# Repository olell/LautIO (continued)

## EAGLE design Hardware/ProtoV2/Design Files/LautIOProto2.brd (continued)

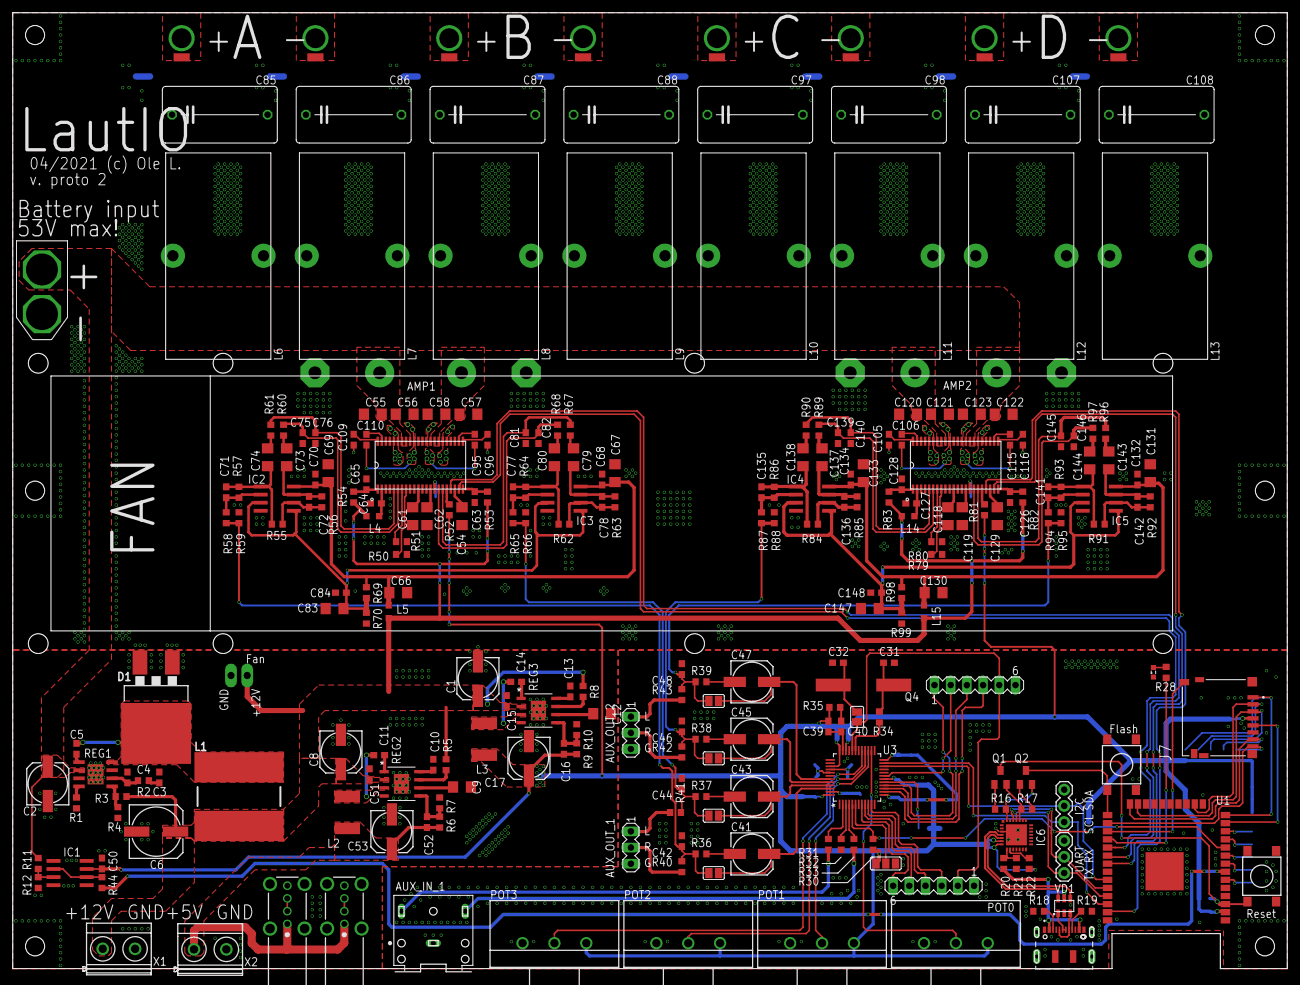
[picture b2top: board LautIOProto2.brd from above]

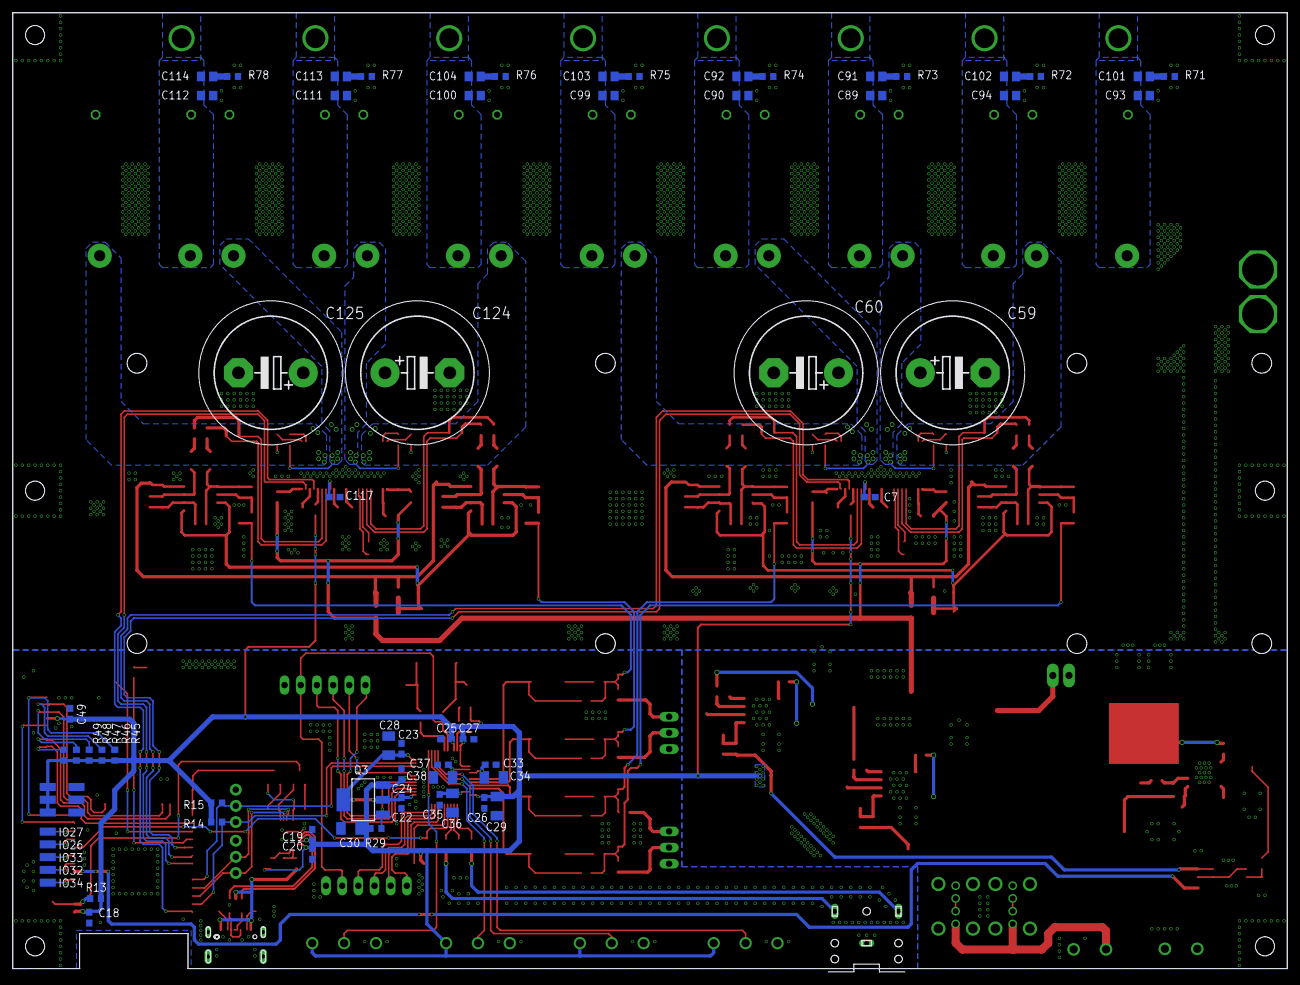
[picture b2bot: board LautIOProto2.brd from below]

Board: 2 copper layers, 200.0 x 150.5 mm, 322 parts (70 on the bottom side), 199 nets.

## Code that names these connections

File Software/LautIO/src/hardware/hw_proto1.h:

/*
 *
 * This file is part of LautIO
 * 
 * Copyright 2021 - olel
 * LautIO is licensed under MIT License
 * See LICENSE file for more information
 * 
 */

#pragma once

// Amp AB Controls
#define AMP_AB_MUTE_PIN    17 // IO17
#define AMP_AB_STANDBY_PIN 16 // IO16

// Amp CD Controls
#define AMP_CD_MUTE_PIN    33 // IO33
#define AMP_CD_STANDBY_PIN 32 // IO32

// DSP Controls
#define DSP_RESET_PIN      14 // IO14

// I2S Output
#define DSP_IN_DATA_PIN    26 // IO26
#define DSP_IN_BCLK_PIN    27 // IO27
#define DSP_IN_LRCLK_PIN   13 // IO13

//#define HARDWARE_HAS_SDCARD // Uncomment on hardware versions which have sd card slots

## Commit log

2021-03-09 Added some files
2021-03-09 Added pdf schematics
2021-03-11 Final Proto V1 hardware filse
2021-03-11 updated bom
2021-03-11 Added platformio software project :)
2021-03-16 Started implementing web base
2021-03-16 Added bootstrap and jquery js files
2021-03-16 Implemented navbar base
2021-03-16 Fixed active highlighting
2021-03-16 Implemented Amp Card with Status pills
2021-03-16 Amp standby & mute controls
2021-03-16 Started implementing about page
2021-03-16 Changed text objects to paths
2021-03-16 Much responsive very wow
2021-03-16 Updated project name
2021-03-17 Add: First config version
2021-03-17 Moved loglevels to log.h
2021-03-17 Added logging functions
2021-03-17 Fixed format string
2021-03-17 Initing logging
2021-03-17 Added include for log.h
2021-03-17 Little platformio change
2021-03-17 Renamed wifi pass fields
2021-03-17 Add: Wifi driver
2021-03-17 Little structure change
2021-03-17 Started implementing filesystem driver
2021-03-17 Add: FSHANDLE
2021-03-17 Little fix
2021-03-17 Add: Load & Store wifi cred in fs
2021-03-17 WIFI AP CONFIG Behavior implemented
2021-03-18 Minor change
2021-03-18 Added wifi init in main
2021-03-18 Started implementing wifi config page
2021-03-18 Responsivess stuff
2021-03-18 Added AsyncWebServer deps
2021-03-18 Started implementation of webserver
2021-03-18 Added network scanning updater
2021-03-26 Added padded logo
2021-03-31 Added gitignore file & excluding test project
2021-03-31 Updated to hotfixed dsp reset pin
2021-03-31 Added reference to sigmadsp library
2021-03-31 Added wire dep
2021-03-31 Removed unused def of M_PI
2021-04-01 Added async webserver regex buildflag
2021-04-01 updated static paths in wifi settings html
2021-04-01 Implemented static file handling
2021-04-01 Added some basic route doc
2021-04-01 Added functions to header
2021-04-01 Implemented set_credentials view
2021-04-01 little bugfix
2021-04-01 fixed invalid links
2021-04-01 Updated twitter link :)
2021-04-01 Added index & about routes/views
2021-04-01 Updated pin definition names
2021-04-04 Added some version definition
2021-04-04 started implementing dsp driver
2021-04-04 little typo
2021-04-04 added wifi cred file to gitignore
2021-04-04 changed dsp software
2021-04-05 Started implementing dsp web controls
2021-04-05 Some basic documentation
2021-04-05 Implemented websocket server + first dsp control
2021-04-06 changed controls file from csv to json
2021-04-06 Added notices of external projects
2021-04-06 Implemented laoding controls.json
2021-04-06 Implemented websocket connection status
2021-04-07 Started implementing soeq
2021-04-07 Wrote quick dev server
2021-04-07 Cosmetic fix
2021-04-07 Decreased connection check interval
2021-04-09 Added tinytemplate to project
2021-04-09 Implemented using tinytemplate.js
2021-04-09 Added IDs to container
2021-04-09 Added dark mode switch
2021-04-09 Changed colors
2021-04-09 Moved & renamed some stuff for spiffs compat
2021-04-09 Added Q input
2021-04-09 Implemented missing soeq controls
2021-04-21 Removed software
2021-04-21 Started re-implementing firmware
2021-04-21 Added license header to main file
2021-04-21 Added my logger
2021-04-21 Initing logger
2021-04-21 Added config.h for static configuration stuff
2021-04-21 Fixed little typo
2021-04-21 Added FILESYSTEM_TYPE switch
2021-04-21 Added filesystem driver - implementing SPIFFS
2021-04-30 New Logo!
2021-04-30 Added new hardware files
2021-04-30 Little change in logging message
2021-05-03 Started implementing amp driver
2021-05-03 minor
2021-05-03 Implemented sd card driver stuff
2021-05-03 Some cleanup & doc comments
2021-05-03 Implemented config singleton base
2021-05-03 Added reference to arduinojson library
2021-05-03 Added sample config file
2021-05-03 renamed get to get_instance
2021-05-03 Initing amps after filesystem
2021-05-03 litl fix
2021-05-03 Implemented config driver
2021-05-03 Removed log level property from example config file
2021-05-03 Removed some left old config
2021-05-03 Added doc for wifi config
2021-05-03 Added required parameters
2021-05-03 Switched this back
2021-05-03 Started implementing wifi driver
2021-05-03 moved wifi to driver
2021-05-03 Added wifi init to setup
2021-05-04 Finished connect function
2021-05-04 Implemented Access Point
2021-05-04 Designed Heatpipe Mount
2021-05-04 Implemented Amp readouts
2021-05-05 Implemented Battery Measurement
2021-05-05 Added FTP Server (EXPERIMENTAL!)
2021-05-05 Removed logging section from config file
2021-05-05 Changed from infinit loop to deepsleep for halt
2021-05-05 Added DSP addr to hardware config
2021-05-05 Added sigmadsp lib ref
2021-05-06 Doc for ftp server conf
2021-05-06 Added mute adc/dac as control type
2021-05-06 Mux ctrl implemented
2021-05-06 2nd order eq implemented
2021-05-06 added types to field descriptions
2021-05-06 Mute DAC implemented
2021-05-06 Mute ADC implemented
2021-05-06 impl dc source ctrl
2021-05-06 impl sine source ctrl
2021-05-06 impl square source ctrl
2021-05-06 copy/past flaws removed
2021-05-06 impl sawtooth ctrl
2021-05-06 impl triangle source ctrl
2021-05-06 impl audio delay ctrl
2021-05-06 removed id param from adc/dac mute
2021-05-06 typo fix
2021-05-06 impl first order eq ctrl
2021-05-06 impl gain ctrl
2021-05-06 impl demux ctrl
2021-05-06 impl soft clip ctrl
2021-05-06 impl hard clip ctrl
2021-05-06 impl compressor rms ctrl
2021-05-06 impl compressor peak ctrl
2021-05-08 Implemented converter script for dsp files
2021-05-08 Added dsp section to config
2021-05-08 Added base firmware
2021-05-08 Implemented firmware loading
2021-05-08 Added name property
2021-05-08 Loading dsp controls json + litte restructure
2021-05-08 Added control wrapper function
2021-05-08 Added wrapper to header
2021-05-08 moved wrapper
2021-05-08 Added http / websocket base
2021-05-08 moved to util
2021-05-08 + interfaces + dsp get controls
2021-05-08 + control update command
2021-05-16 Moved some files + panels
2021-05-16 logo background transparancy
2021-05-17 Little update in command
2021-05-17 Added amp interface handler
2021-05-17 Updated hardware config to current prototype
2021-05-20 Added case design files
2021-05-20 + config interface
2021-05-20 Started implementing system interface
2021-05-22 Added test_connection command in sys sec
2021-05-22 Minor bug prevention
2021-05-22 Started implementing webinterface
2021-05-29 Updated dep licenses
2021-05-30 Changed dep to current git version
2021-05-30 Changed from JsonObject to DynamicJsonDocument and some minor
2021-05-30 Fixed this sh*tty memory error and some code improvement
2021-05-30 Added case rendering images
2021-05-30 Responsiveness + soec + appstuff
2021-05-31 Minor errors fixed
2021-05-31 Individual functions for control rendering
2021-05-31 Some init values from control object
2021-05-31 Little mobile app tweaks
2021-05-31 Changed from DJD to JsonObject
2021-05-31 Added super basic app icon
2021-05-31 Doc for DSP interface
2021-05-31 Removed unused function
2021-05-31 Added send_all functionality
2021-05-31 Fixed vbat read offset
2021-05-31 Added battery voltage to boot log
2021-05-31 Added text option to send_all
2021-06-14 Moved stuff to update_soeq_ui method
2021-06-14 Created abstract control template
2021-06-20 Split amp interface
2021-06-20 Sending amp status to clients
2021-07-02 Saving some memory
2021-07-02 Removed
2021-07-13 Added compat for wifi without password
2021-07-14 Added ui interface
2021-07-14 Removed only qc + added get config
2021-07-14 changed to ui_config
2021-07-14 Ui config + quick control filtering
2021-07-14 Added controls template
2021-07-15 implemented static serving of webinterface
2021-07-15 Added menu dots
2021-07-15 more ignores
2021-07-15 Started implementing settings modal
2021-07-15 Changed from ctrl.name to ctrl.id as identifier
2021-07-15 Settings functionality: name, ro, change
2021-07-15 Closing modal on save changes
2021-07-17 Implemented custom webui serving
2021-07-18 Added both amp on/off switches
2021-07-20 Added missing filter types
2021-07-28 Modified config response
2021-07-28 Added dsp config request
2021-08-06 Restructured javascript
2021-08-06 Saving controls implemented
2021-10-12 Implemented debug console
2021-10-12 Added settings page w/ debug button
2021-10-14 Little changes in debug console
2021-10-14 Fetching new amp state directly after update
2021-10-14 Added connection status badge
